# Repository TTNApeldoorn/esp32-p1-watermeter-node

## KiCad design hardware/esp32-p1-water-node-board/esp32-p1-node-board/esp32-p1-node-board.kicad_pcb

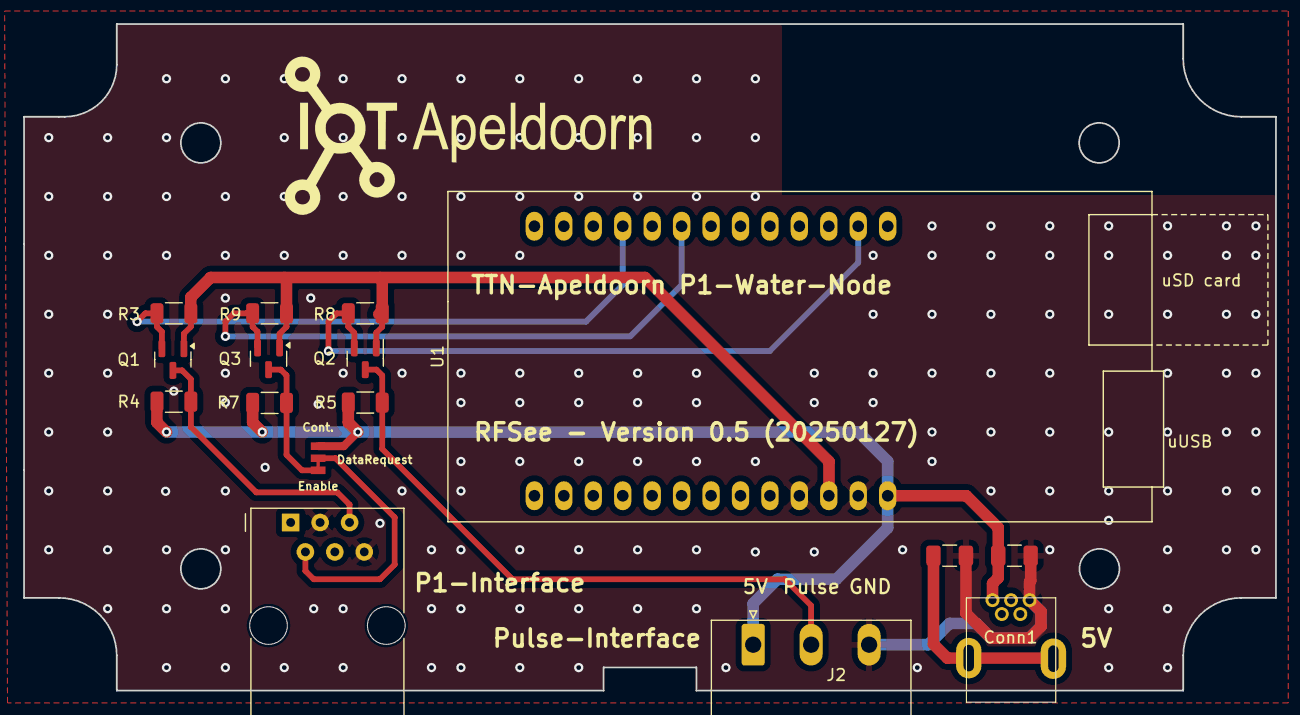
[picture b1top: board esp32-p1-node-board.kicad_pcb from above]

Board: 2 copper layers, 108.0 x 57.5 mm, 16 parts (0 on the bottom side), 11 nets.

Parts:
C2, C3: 10n; C_1206_3216Metric
Conn1: THT_USB-B-Mini
J1: RJ11-6; RJ12_Amphenol_54601
J2: Conn_01x03; PhoenixContact_MSTBA_2,5_3-G_1x03_P5.00mm_Horizontal
JP1: Jumper_3_NC-1_Trace_NoSilk
Q1, Q2, Q3: BSS138; SOT-23
R3, R4, R5, R7, R8, R9: 10K; R_1206_3216Metric
U1: TTGO_T3_V1.6.1

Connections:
/3V3: Q1.1 (G), Q2.1 (G), Q3.1 (G), R3.1, R8.1, R9.1, U1.11 (3V3)
/5V: C2.1, Conn1.1 (VCC), J2.1, JP1.3, R4.1, R5.1, R7.1, U1.13 (5V)
/DATA_P1: J1.5, Q1.3 (D), R4.2
/DATA_P1_3V3: Q1.2 (S), R3.2, U1.23 (IO34)
/DATA_P1_GND: C2.2, C3.1, Conn1.5 (GND), J1.3, J1.6, J2.3, U1.10 (GND), U1.12 (GND)
/DATA_P1_REQ: J1.2, JP1.2 (C)
/DATA_P1_REQ_3V3: Q3.2 (S), R9.2, U1.21 (IO14)
/PULSE_WATER: J2.2, Q2.3 (D), R5.2
/PULSE_WATER_3V3: Q2.2 (S), R8.2, U1.15 (IO04)
unnamed: C3.2, Conn1.6 (Shield), Conn1.7 (Shield)
unnamed: JP1.1 (A), Q3.3 (D), R7.2

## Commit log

2024-10-23 Added kicad library pe1mew
2024-10-24 Corrections on circuit
2024-10-30 Add docs and BOM
2024-10-31 Updated files to KiCad 8.0
2024-11-17 Start design PCB
2024-11-18 Final PCB design voor proef
2024-11-21 platformio source files
    prototype version
2025-01-27 Updated PCB to version 0.5
